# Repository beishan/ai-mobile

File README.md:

# AI Mobile E-Ink Reader

ESP32-S3 reader firmware and desktop simulators for selectable black/white E-Ink panels.

Current hardware target:

- MCU: ESP32-S3 N16R8.
- Panels: OSPTEK 4.26 inch 480 x 800 (default), or HINK-E037A03-A1 3.7 inch 240 x 416.
- Driver ICs: SSD1677 or UC8171/IL0324.
- Display interface: SPI.
- Framebuffer: one 1bpp black/white plane, 48,000 bytes per frame.

The project is now reader-first. The old game module has been removed from the shared app state, home screen, renderer, and simulator flow.

## Build

```bash
make reader_sim
make reader_sim_sdl
```

## Test

```bash
make test
```

## Run

SDL2 windowed simulator:

```bash
./reader_sim_sdl
```

PPM export simulator:

```bash
./reader_sim
```

Controls:

- `w` / Up: up or previous item.
- `s` / Down: down or next item.
- `h`, Space, or Enter: home/select.
- `b` or Esc: back.
- `p` or Backspace: power.
- `q`: quit.

The headless simulator writes the latest 480 x 800 frame to `out/frame.ppm`.

## Current Modules

- Home: six app entries, `阅读 / 文件 / 天气 / 日历 / 英语 / 设置`.
- Files: browses `/sdcard`, enters folders, returns to parent folders, and opens selected UTF-8 `.txt` files in the reader.
- Bookshelf: lists TXT and EPUB books indexed from the SD card, with per-book progress and bookmarks.
- Reader: SD-backed TXT/EPUB reader with page turning, catalog, bookmarks, font size, and line spacing settings.
- Persistence: portable snapshot codec for per-book progress, bookmarks, recent book, and reader/settings state; simulators load it from `out/app_state.txt`, and ESP32 firmware stores the same payload in NVS.
- Back: the dedicated BACK key returns to the parent page; POWER long press saves app state and requests display sleep.
- Weather: mock city switching, refresh state, WiFi/offline cache behavior.
- Calendar: month switching and selected-day detail strip.
- English: front/back word card, known/review counts, answer-state dots.
- Settings: font size, line spacing, WiFi, city, and power-saving state.
- About: ESP32-S3 N16R8 plus 4.26 inch 480 x 800 SSD1677 SPI panel target.

## ESP32 Firmware

The PlatformIO + ESP-IDF firmware reuses the same portable `gfx`, `font`, `app`, and `ui` modules as the simulators.

Build firmware:

```bash
pio run -e esp32-n16r8
```

Build the HINK-E037A03-A1 firmware:

```bash
pio run -e esp32-n16r8-hink-e037a03-a1
```

The HINK target keeps the 480 x 800 logical UI and scales its 1bpp output to
the native 240 x 416 portrait panel. Its physical frame is 12,480 bytes and
BUSY is active-low. Use the same GPIO-level SPI signals listed below when the
panel is connected through a compatible 24-pin EPD power/adapter circuit.
Do not plug the bare HINK FPC into the existing SSD1677 PCB until its FPC pinout
and high-voltage reference circuit have been checked against the exact panel
datasheet.

Upload firmware:

```bash
pio run -e esp32-n16r8 -t upload
```

Monitor serial logs:

```bash
pio device monitor -e esp32-n16r8
```

Hardware status:

- `src/platform/epd_panel.h` selects panel geometry, controller family, frame size, and BUSY polarity at compile time.
- `src/platform/esp_board_config.h` centralizes the shared SPI wiring and timing constants.
- `src/platform/epd_frame.c` packs the shared framebuffer into the selected panel's black/white 1bpp plane.
- `src/platform/ssd1677.c` implements SSD1677 reset-time setup, RAM addressing, full-frame transfer, refresh, BUSY synchronization, power-off, and deep sleep.
- `src/platform/il0324.c` implements the HINK 240 x 416 UC8171/IL0324 command sequence, full/partial transfer, refresh, and sleep.
- `src/platform/esp_display.c` connects the selected controller to ESP-IDF GPIO/SPI.
- `src/platform/esp_input.c` scans BACK/POWER/UP/HOME/DOWN in a dedicated 20ms FreeRTOS task, applies 40ms debounce, and queues events while E-Ink refresh blocks the UI loop.
- `src/platform/esp_sd.c` mounts a FAT-formatted SPI SD card at `/sdcard`; startup indexes alphabetically sorted `.txt` and `.epub` files from `/sdcard/books`.
- POWER long press is detected after 1200ms, synchronously saves reading state, sleeps the SSD1677, stops Wi-Fi/Web services, and enters GPIO-wakeable light sleep.
- `src/app/reader_library.c` indexes SD TXT and EPUB files used by the bookshelf and reader. EPUB package metadata and spine-ordered XHTML are extracted into a hidden SD cache, then the shared paginator keeps page offsets (up to 2,048 reader pages per book).
- `src/app/app_persistence.c` captures durable app state into a versioned text payload, with simulator file save/load wired through `out/app_state.txt` and ESP32 NVS save/load wired through the `reader/app_state` key.
- The desktop simulators load TXT and EPUB files from `assets/books/realbook`; no built-in book-text fallback is provided.
- Text sources may use form-feed (`\f`) for explicit page breaks; plain text without page breaks is split automatically on UTF-8-safe boundaries.
- The 480 x 800 UI framebuffer is allocated from PSRAM instead of the ESP-IDF main-task stack.
- The SSD1677 display layer keeps a 48,000-byte previous-frame cache in PSRAM and derives one byte-aligned dirty rectangle from actual framebuffer differences. Unchanged frames are skipped, small changes use one differential partial refresh, and generic UI changes covering at least 70% of the panel use a full refresh. Entering the reader and turning text pages explicitly use a partial refresh for the reader area; the cumulative ghosting limit still promotes an occasional update to a full refresh.
- Partial refreshes are counted globally by the display driver. A full refresh clears ghosting after either 24 consecutive partial updates or roughly 12 screenfuls of cumulative updated area. Reader pages therefore normally remain partial for about 12 page turns; adjust `ESP_EPD_PARTIAL_REFRESH_LIMIT` or `ESP_EPD_PARTIAL_AREA_SCREENS` in `esp_board_config.h` if the panel needs a different interval.
- TXT/EPUB pagination follows the selected font size/family, line spacing, margins, indentation, and bold width. Chapter-like lines are indexed for catalog navigation, progress/bookmarks are matched by stable book IDs instead of shelf position, and files exceeding 2,048 laid-out pages show an explicit truncation warning.
- Opening a newly indexed book exposes its first 16 pages immediately and continues full-book pagination on the other CPU core. Rendering a page synchronously caches the next ready page, and background progress never triggers an E-Ink refresh by itself, so page turns within the ready range remain responsive.
- Wi-Fi + NTP time sync is ready. Open Settings and press HOME to edit SSID/password on the device. With battery saving enabled, Wi-Fi turns off after boot-time sync/weather work and is restarted only for Wi-Fi settings, manual sync, or scheduled weather; the Web admin follows the same lifecycle.
- Battery saving enables 40–160MHz dynamic frequency scaling and automatic tickless light sleep. After 30 seconds without input and once background work is idle, the device enters GPIO-wakeable light sleep with a 10-minute maintenance wake. Non-interactive reader status clocks update every 10 minutes, or every 30 minutes below 15% battery; automatic weather refresh is disabled below 15%.

Current E-Ink wiring:

| EPD pin | ESP32 pin |
|---------|-----------|
| BUSY | GPIO4 |
| RST | GPIO16 |
| DC | GPIO15 |
| CS | GPIO5 |
| SCK | GPIO18 |
| SDA/MOSI | GPIO17 |
| GND | GND |
| VCC | 3V |

Current button wiring:

| Button | ESP32 pin | Note |
|--------|-----------|------|
| BACK | GPIO42 | Internal pull-up; button connects to GND |
| POWER | GPIO41 | External 10k pull-up to 3.3V |
| UP | GPIO38 | External 10k pull-up to 3.3V |
| HOME | GPIO39 | External 10k pull-up to 3.3V |
| DOWN | GPIO40 | External 10k pull-up to 3.3V |

Current SD expansion-board wiring:

| SD pin | ESP32-S3 pin | Note |
|--------|----------------|------|
| CS | GPIO13 | Dedicated SD chip select |
| MOSI | GPIO17 | Shared with E-Ink SDA/MOSI |
| CLK | GPIO18 | Shared with E-Ink SCK |
| MISO | GPIO21 | SD data back to ESP32-S3 |
| GND | GND | Common ground |
| VCC | 3V3 | Use a 3.3V-compatible module |

Format the card as FAT32 and place UTF-8 text files under `/books`. The SD module
normally provides the required SPI pull-ups; if yours does not, add external
10k pull-ups as required by the card/module design.

## Font Asset

The simulator uses tracked bitmap font assets in `assets/fonts/` so host output stays deterministic.

To regenerate them on macOS:

```bash
python3 tools/generate_font.py
```

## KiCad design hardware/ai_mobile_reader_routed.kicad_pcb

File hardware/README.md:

# AI 移动阅读器 PCB——A 版

本目录保存 4.26 英寸竖屏墨水阅读器的硬件设计，主要组成如下：

- ESP32-S3-WROOM-1-N16R8 模组；
- OSPTEK 4.26 英寸、480 × 800 黑白墨水屏，SSD1677 控制器，24Pin、
  0.5 mm 间距 FPC；
- 一节带保护板的 3.7 V 锂离子/锂聚合物电池，使用 JST-PH-2 接口；
- BQ24074 电源路径充电芯片及 TPS63031 3.3 V 升降压稳压器；
- ESP32-S3 原生 USB，通过 USB-C 接口连接电脑和刷写固件；
- 外接五按键接口及板载 MicroSD 卡座。

## 机械设计约定

- 四层板，厚度 1.6 mm，尺寸 58 × 102 mm，设计为安装在屏幕后方；
- 屏幕排线金手指面与屏幕正面方向一致；J3 安装在 PCB 背面，使用下接点
  连接器，丝印已标出 Pin 1 及金手指方向；
- USB-C 从 PCB 底边伸出，MicroSD 卡从右侧插入，按键接口位于右侧；
- 当前安装位置适合作为样机默认布局，尚未针对最终外壳进行结构定型。

## 安全及首次上电检查

- 只能使用带保护板的单节锂电池；
- 通电状态下禁止插拔墨水屏 FPC；
- 安装屏幕前，确认 J3 的 6、7、8、17 脚均为 GND，并用实物再次核对
  连接器接触面和 Pin 1 方向；
- 第一次上电使用带限流功能的实验电源，先确认 3.3 V 正常，再安装屏幕；
- 屏幕刷新时通过 TP5～TP8 检查 GDR、RESE、PREVGH 和 PREVGL；
- 墨水屏高压电路采用 SSD1677 参考拓扑，C12～C23 必须使用 X5R/X7R、
  耐压不低于 25 V 的电容。

## 文件说明

- `ai_mobile_reader_routed.kicad_pcb`：已经完成布线的 KiCad PCB，用于检查和生产；
- `ai_mobile_reader.kicad_pcb`：自动生成的未布线布局，作为可重复生成的布线输入；
- `SCHEMATIC.md`：完整引脚表、电气连接及接口定义；
- `bom.csv`：器件清单；
- `manufacturing/`：Gerber、钻孔、贴片坐标和生产说明；
- `reports/`：DRC 报告及 PCB 正反面渲染图。

## 重新生成 PCB

生成脚本依赖 KiCad 自带的 Python 和 `pcbnew` 模块。本机命令如下：

```sh
PY='/Volumes/KiCad/KiCad/KiCad.app/Contents/Frameworks/Python.framework/Versions/3.9/bin/python3'
PYTHONPATH='/Volumes/KiCad/KiCad/KiCad.app/Contents/Frameworks/Python.framework/Versions/3.9/lib/python3.9/site-packages' \
DYLD_LIBRARY_PATH='/Volumes/KiCad/KiCad/KiCad.app/Contents/Frameworks' \
"$PY" hardware/generate_board.py
```

布线、DRC 检查及生产文件导出要求见 `manufacturing/README.md`。

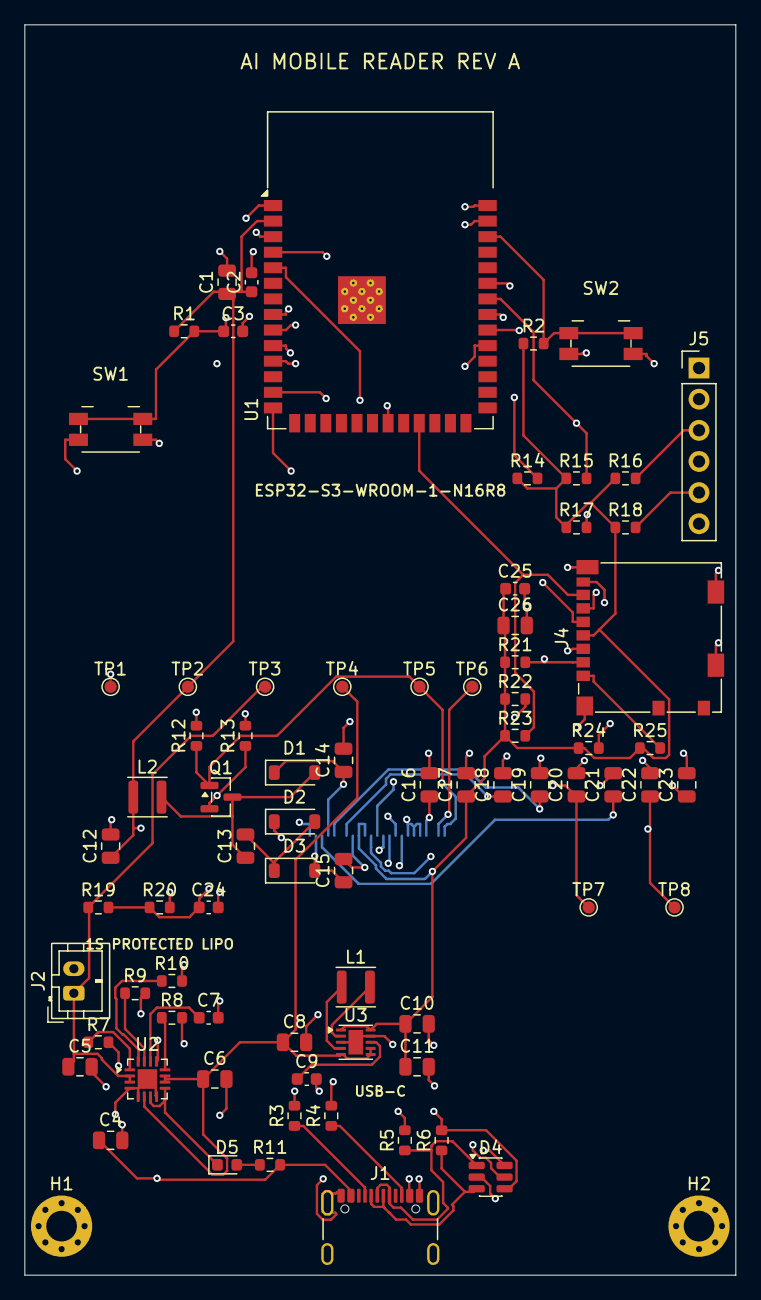
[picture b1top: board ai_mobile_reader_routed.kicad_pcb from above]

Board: 4 copper layers, 58.0 x 102.0 mm, 79 parts (1 on the bottom side), 50 nets.

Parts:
C1, C26: 10uF/6.3V; C_0805_2012Metric
C2, C7, C9, C24, C25: 100nF; C_0603_1608Metric
C3: 1uF; C_0603_1608Metric
C4: 1uF/10V; C_0805_2012Metric
C5, C6: 4.7uF/10V; C_0805_2012Metric
C8, C10, C11: 10uF/10V; C_0805_2012Metric
C12, C13, C14, C15, C16, C19, C20, C21, C22: 4.7uF/25V; C_0805_2012Metric
C17, C18, C23: 1uF/25V; C_0805_2012Metric
D1, D2, D3: MBR0530; D_SOD-123
D4: USBLC6-2SC6; SOT-23-6
D5: CHARGE_AMBER; LED_0603_1608Metric
H1, H2: M2.5; MountingHole_2.5mm_Pad_Via
J1: USB-C; USB_C_Receptacle_GCT_USB4105-xx-A_16P_TopMnt_Horizontal
J2: 1S_PROTECTED_LIPO; JST_PH_B2B-PH-K_1x02_P2.00mm_Vertical
J3: OSPTEK_4.26IN_24PIN; Hirose_FH12-24S-0.5SH_1x24-1MP_P0.50mm_Horizontal
J4: Molex 104031-0811 MicroSD; microSD_HC_Molex_104031-0811
J5: EXTERNAL_KEYS; PinHeader_1x06_P2.54mm_Vertical
L1: 1.5uH >=1.5A; L_APV_ANR3015
L2: 47uH 500mA; L_APV_ANR3015
Q1: AO3400A 30V; SOT-23
R1, R2, R7, R14, R15, R16, R17, R18, R21, R22, R23: 10k; R_0603_1608Metric
R3, R4: 5.1k; R_0603_1608Metric
R5, R6: 22R; R_0603_1608Metric
R8: 3.24k 1%; R_0603_1608Metric
R9: 1.8k 1%; R_0603_1608Metric
R10: 1.78k 1%; R_0603_1608Metric
R11: 1k; R_0603_1608Metric
R12, R19: 1M; R_0603_1608Metric
R13: 2.2R 1%; R_0603_1608Metric
R20: 330k; R_0603_1608Metric
R24, R25: 47k; R_0603_1608Metric
SW1: RESET; Panasonic_EVQPUJ_EVQPUA
SW2: BOOT; Panasonic_EVQPUJ_EVQPUA
TP1: GND; TestPoint_Pad_D1.0mm
TP2: +3V3; TestPoint_Pad_D1.0mm
TP3: VBAT; TestPoint_Pad_D1.0mm
TP4: SYS; TestPoint_Pad_D1.0mm
TP5: EPD_GDR; TestPoint_Pad_D1.0mm
TP6: EPD_RESE; TestPoint_Pad_D1.0mm
TP7: PREVGH; TestPoint_Pad_D1.0mm
TP8: PREVGL; TestPoint_Pad_D1.0mm
U1: ESP32-S3-WROOM-1-N16R8; ESP32-S3-WROOM-1
U2: BQ24074RGT; VQFN-16-1EP_3x3mm_P0.5mm_EP1.6x1.6mm
U3: TPS63031DSK; WSON-10-1EP_2.5x2.5mm_P0.5mm_EP1.2x2mm

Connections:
+3V3: C1.1, C2.1, C10.1, C11.1, C12.1, C17.1, C25.1, C26.1, J3.15, J3.16, J4.4, L2.1, R1.1, R2.1, R14.1, R15.1, R16.1, R17.1, R18.1, R21.1, R22.1, R23.1, R24.1, R25.1, TP2.1, U1.2, U3.1, U3.10
BAT_ADC: C24.1, R19.2, R20.1, U1.39
BOOST_FLY: C13.2, D2.2, D3.1
BOOST_SW: C13.1, D1.2, L2.2, Q1.3
BOOT: R2.2, SW2.1, U1.38
BQ_CHG: D5.1, U2.7, U2.9
BQ_ILIM: R8.1, U2.12
BQ_ISET: R10.1, U2.16
BQ_ITERM: R9.1, U2.15
BQ_TMR: C7.1, U2.14
BQ_TS: R7.1, U2.1
BTN_BACK: J5.1, R14.2, U1.35
BTN_DOWN: J5.5, R18.2, U1.33
BTN_HOME: J5.4, R17.2, U1.32
BTN_POWER: J5.2, R15.2, U1.34
BTN_UP: J5.3, R16.2, U1.31
CC1: J1.A5, R3.1
CC2: J1.B5, R4.1
EN: C3.1, R1.2, SW1.1, U1.3
EPD_BUSY: J3.9, U1.4
EPD_CS: J3.12, U1.5
EPD_DC: J3.11, U1.8
EPD_GDR: J3.2, Q1.1, R12.1, TP5.1
EPD_RESE: J3.3, Q1.2, R13.1, TP6.1
EPD_RST: J3.10, U1.9
EPD_VCOM: C23.1, J3.24
EPD_VDD: C18.1, J3.18
EPD_VSH1: C19.1, J3.20
EPD_VSH2: C16.1, J3.5
EPD_VSL: C21.1, J3.22
GND: C1.2, C2.2, C3.2, C4.2, C5.2, C6.2, C7.2, C8.2, C9.2, C10.2, C11.2, C12.2, C14.2, C15.2, C16.2, C17.2, C18.2, C19.2, C20.2, C21.2, C22.2, C23.2, C24.2, C25.2, C26.2, D2.1, D4.2, H1.1, H2.1, J1.A1, J1.A12, J1.B1, J1.B12, J1.SH, J2.2, J3.6, J3.7, J3.8, J3.17, J4.6, J4.SH, J5.6, R3.2, R4.2, R7.2, R8.2, R9.2, R10.2, R12.2, R13.2, R20.2, SW1.2, SW2.2, TP1.1, U1.1, U1.40, U1.41, U2.4, U2.5, U2.8, U2.17, U3.3, U3.9, U3.11
LED_CHG_A: D5.2, R11.1
PREVGH: C14.1, C20.1, D1.1, J3.21, TP7.1
PREVGL: C15.1, C22.1, D3.2, J3.23, TP8.1
REG_L1: L1.1, U3.4
REG_L2: L1.2, U3.2
REG_VINA: C9.1, U3.8
SD_CS: J4.2, R21.2, U1.21
SD_DAT1: J4.8, R24.2
SD_DAT2: J4.1, R25.2
SD_MISO: J4.7, R23.2, U1.23
SPI_MOSI: J3.14, J4.3, R22.2, U1.10
SPI_SCK: J3.13, J4.5, U1.11
SYS: C6.1, C8.1, TP4.1, U2.6, U2.10, U2.11, U3.5, U3.6, U3.7
USB_D+: D4.6, R5.2, U1.14
USB_D+_MCU: D4.1, J1.A6, J1.B6, R5.1
USB_D-: D4.4, R6.2, U1.13
USB_D-_MCU: D4.3, J1.A7, J1.B7, R6.1
USB_VBUS: C4.1, D4.5, J1.A4, J1.A9, J1.B4, J1.B9, R11.2, U2.13
VBAT: C5.1, J2.1, R19.1, TP3.1, U2.2, U2.3

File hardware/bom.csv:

位号,参数 / 厂家料号,封装,装配状态
C1,10uF/6.3V,C_0805_2012Metric,装配
C10,10uF/10V,C_0805_2012Metric,装配
C11,10uF/10V,C_0805_2012Metric,装配
C12,4.7uF/25V,C_0805_2012Metric,装配
C13,4.7uF/25V,C_0805_2012Metric,装配
C14,4.7uF/25V,C_0805_2012Metric,装配
C15,4.7uF/25V,C_0805_2012Metric,装配
C16,4.7uF/25V,C_0805_2012Metric,装配
C17,1uF/25V,C_0805_2012Metric,装配
C18,1uF/25V,C_0805_2012Metric,装配
C19,4.7uF/25V,C_0805_2012Metric,装配
C2,100nF,C_0603_1608Metric,装配
C20,4.7uF/25V,C_0805_2012Metric,装配
C21,4.7uF/25V,C_0805_2012Metric,装配
C22,4.7uF/25V,C_0805_2012Metric,装配
C23,1uF/25V,C_0805_2012Metric,装配
C24,100nF,C_0603_1608Metric,装配
C3,1uF,C_0603_1608Metric,装配
C4,1uF/10V,C_0805_2012Metric,装配
C5,4.7uF/10V,C_0805_2012Metric,装配
C6,4.7uF/10V,C_0805_2012Metric,装配
C7,100nF,C_0603_1608Metric,装配
C8,10uF/10V,C_0805_2012Metric,装配
C9,100nF,C_0603_1608Metric,装配
D1,MBR0530,D_SOD-123,装配
D2,MBR0530,D_SOD-123,装配
D3,MBR0530,D_SOD-123,装配
D4,USBLC6-2SC6,SOT-23-6,装配
D5,CHARGE_AMBER,LED_0603_1608Metric,装配
J1,USB-C,USB_C_Receptacle_GCT_USB4105-xx-A_16P_TopMnt_Horizontal,装配
J2,1S_PROTECTED_LIPO,JST_PH_B2B-PH-K_1x02_P2.00mm_Vertical,装配
J3,OSPTEK_4.26IN_24PIN,Hirose_FH12-24S-0.5SH_1x24-1MP_P0.50mm_Horizontal,装配
J4,SD_MODULE_2X8,PinHeader_2x08_P2.54mm_Vertical,装配
J5,EXTERNAL_KEYS,PinHeader_1x06_P2.54mm_Vertical,装配
L1,1.5uH >=1.5A,L_APV_ANR3015,装配
L2,47uH 500mA,L_APV_ANR3015,装配
Q1,AO3400A 30V,SOT-23,装配
R1,10k,R_0603_1608Metric,装配
R10,1.78k 1%,R_0603_1608Metric,装配
R11,1k,R_0603_1608Metric,装配
R12,1M,R_0603_1608Metric,装配
R13,2.2R 1%,R_0603_1608Metric,装配
R14,10k,R_0603_1608Metric,装配
R15,10k,R_0603_1608Metric,装配
R16,10k,R_0603_1608Metric,装配
R17,10k,R_0603_1608Metric,装配
R18,10k,R_0603_1608Metric,装配
R19,1M,R_0603_1608Metric,装配
R2,10k,R_0603_1608Metric,装配
R20,330k,R_0603_1608Metric,装配
R3,5.1k,R_0603_1608Metric,装配
R4,5.1k,R_0603_1608Metric,装配
R5,22R,R_0603_1608Metric,装配
R6,22R,R_0603_1608Metric,装配
R7,10k,R_0603_1608Metric,装配
R8,3.24k 1%,R_0603_1608Metric,装配
R9,1.8k 1%,R_0603_1608Metric,装配
SW1,RESET,Panasonic_EVQPUJ_EVQPUA,装配
SW2,BOOT,Panasonic_EVQPUJ_EVQPUA,装配
U1,ESP32-S3-WROOM-1-N16R8,ESP32-S3-WROOM-1,装配
U2,BQ24074RGT,VQFN-16-1EP_3x3mm_P0.5mm_EP1.6x1.6mm,装配
U3,TPS63031DSK,WSON-10-1EP_2.5x2.5mm_P0.5mm_EP1.2x2mm,装配

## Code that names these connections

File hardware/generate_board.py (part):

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

# External five-key harness: BACK, POWER, UP, HOME, DOWN, common GND.
load_fp("Connector_PinHeader_2.54mm", "PinHeader_1x06_P2.54mm_Vertical", "J5", "EXTERNAL_KEYS", 56, 29, pads={"1": "BTN_BACK", "2": "BTN_POWER", "3": "BTN_UP", "4": "BTN_HOME", "5": "BTN_DOWN", "6": "GND"})
button_pullups = (
    ("BTN_BACK", 42, 38), ("BTN_POWER", 46, 38), ("BTN_UP", 50, 38),
    ("BTN_HOME", 46, 42), ("BTN_DOWN", 50, 42),
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
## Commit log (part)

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2026-06-17 Add reader simulator design spec
2026-06-17 docs: add reader simulator implementation plan
2026-06-17 feat: add simulator framebuffer primitives
2026-06-17 feat: add simulator ppm display output
2026-06-17 feat: add reader simulator app state
2026-06-17 feat: render simulator ui pages
2026-06-17 feat: add interactive reader simulator
2026-06-17 docs: document reader simulator
2026-06-17 docs: add chinese simulator design spec
2026-06-17 docs: add chinese simulator implementation plan
2026-06-17 feat: add utf8 font api
2026-06-17 feat: add chinese bitmap font asset
2026-06-17 feat: render simulator pages with chinese font
2026-06-17 feat: add chinese simulator module flows
2026-06-17 docs: document chinese simulator
2026-06-17 docs: add sdl2 simulator plan
2026-06-17 feat: add sdl2 simulator window
2026-06-17 更换模拟器
2026-06-18 feat: build reader simulator and esp32 firmware skeleton
2026-06-18 feat: 解决ESP 真机按键输入
2026-06-22 Retarget reader to 480x800 SSD677 panel
2026-06-23 feat: retarget UI layout to 480x800 portrait panel
    - Add shared layout constants (PAGE_MARGIN_X, CONTENT_WIDTH, BODY_TOP,
    BODY_BOTTOM, BODY_HEIGHT) in pages.c to centralize positioning.
    - Home: rearrange to 3 rows x 2 columns grid filling content area.
    - Weather: large temperature hero block, full-width forecast cards,
    full-width air quality bar.
    - Calendar: enlarged weekday header and day cells (80px row height),
2026-06-23 feat: 迭代功能
2026-06-29 feat: 完成部分功能
